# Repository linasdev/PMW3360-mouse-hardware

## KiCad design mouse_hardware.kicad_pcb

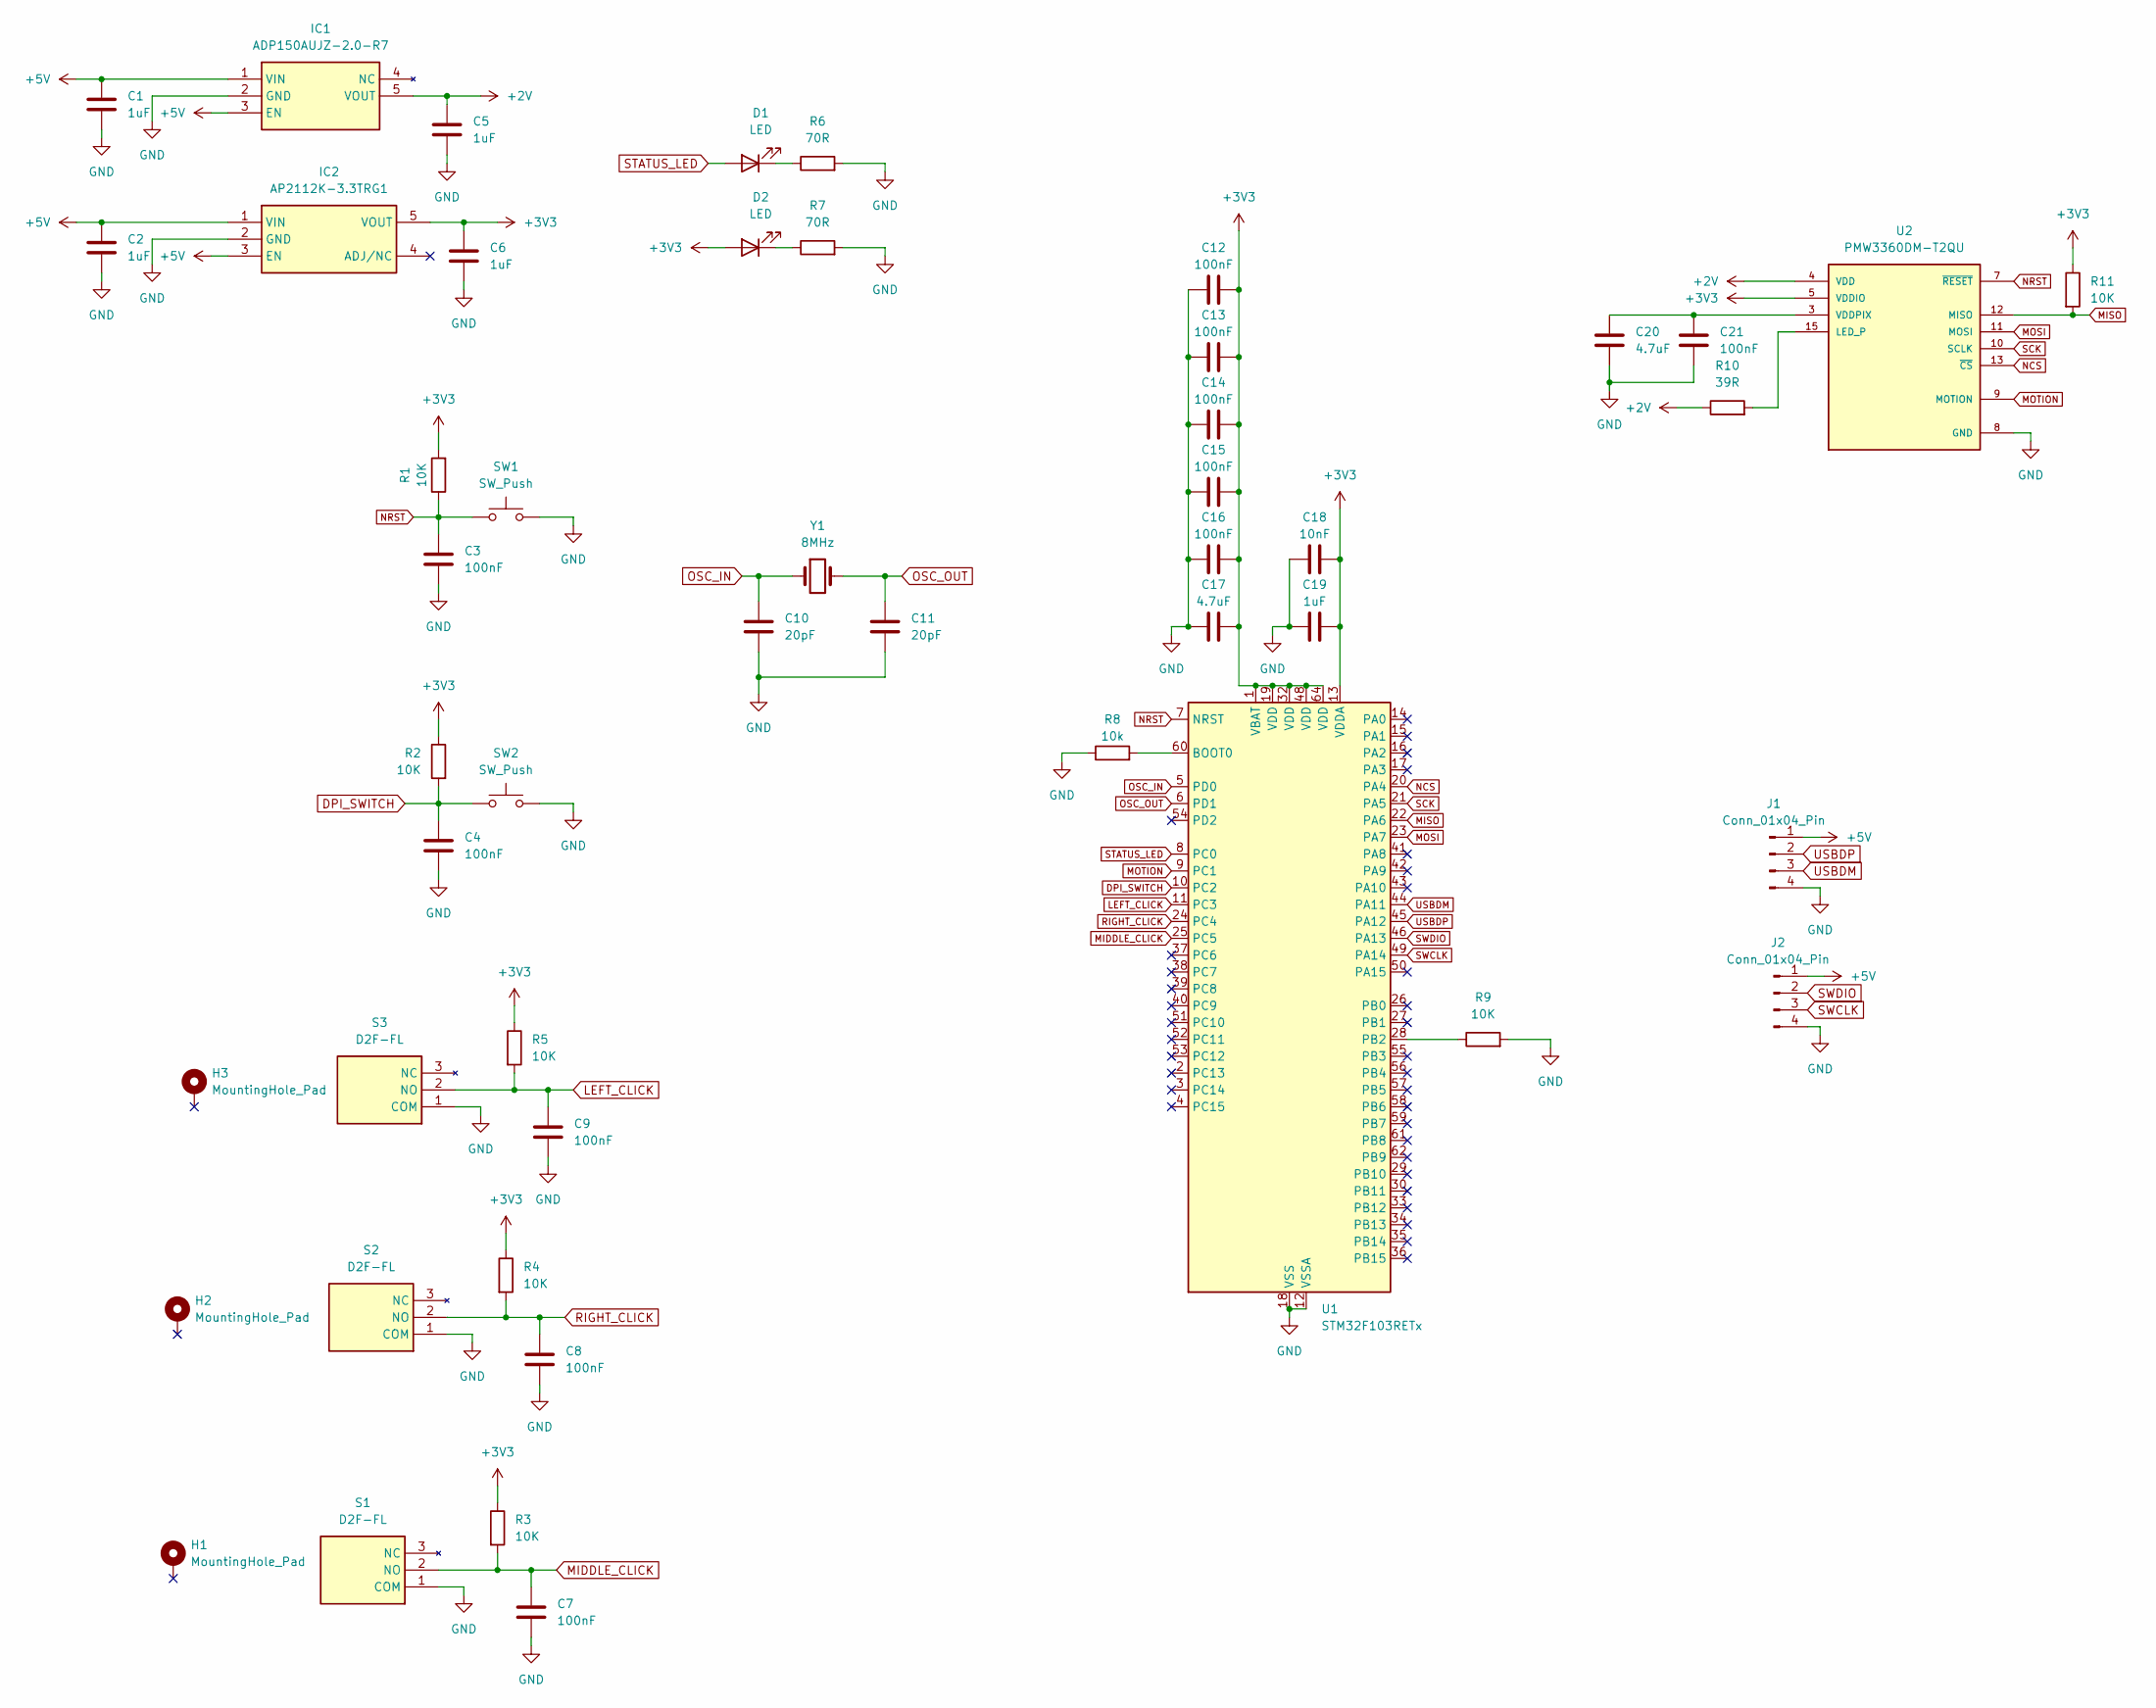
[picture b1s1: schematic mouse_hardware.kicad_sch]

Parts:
C1, C2, C5, C6, C19: 1uF; C_0805_2012Metric_Pad1.18x1.45mm_HandSolder
C3, C4, C7, C8, C9, C12, C13, C14, C15, C16, C21: 100nF; C_0805_2012Metric_Pad1.18x1.45mm_HandSolder
C10, C11: 20pF; C_0805_2012Metric_Pad1.18x1.45mm_HandSolder
C17, C20: 4.7uF; C_0805_2012Metric_Pad1.18x1.45mm_HandSolder
C18: 10nF; C_0805_2012Metric_Pad1.18x1.45mm_HandSolder
D1, D2: LED; LED_0805_2012Metric_Pad1.15x1.40mm_HandSolder
H1, H2, H3: MountingHole_Pad; Hole_1.8mm_1.2mm
IC1: ADP150AUJZ-2.0-R7; SOT95P280X100-5N; Mouser Part Number 584-ADP150AUJZ2.0R7
IC2: AP2112K-3.3TRG1; SOT95P282X130-5N; Mouser Part Number 621-AP2112K-3.3TRG1
J1, J2: Conn_01x04_Pin; PinHeader_1x04_P2.54mm_Horizontal
R1, R2, R3, R4, R5, R9, R11: 10K; R_0805_2012Metric_Pad1.20x1.40mm_HandSolder
R6, R7: 70R; R_0805_2012Metric_Pad1.20x1.40mm_HandSolder
R8: 10k; R_0805_2012Metric_Pad1.20x1.40mm_HandSolder
R10: 39R; R_0805_2012Metric_Pad1.20x1.40mm_HandSolder
S1, S2, S3: D2F-FL; D2FFL; Mouser Part Number 653-D2F-FL
SW1, SW2: SW_Push; 1478731
U1: STM32F103RETx; LQFP-64_10x10mm_P0.5mm
U2: PMW3360DM-T2QU; PMW3360; MANUFACTURER_PART_NUMBER PMW3360DM-T2QU
Y1: 8MHz; Crystal_SMD_HC49-SD_HandSoldering

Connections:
+2V: C5.2, IC1.5 (VOUT), R10.1, U2.4 (VDD)
+3V3: C6.2, C12.1, C13.1, C14.1, C15.1, C16.1, C17.1, C18.1, C19.1, D2.2 (A), IC2.5 (VOUT), R1.2, R2.1, R3.1, R4.1, R5.1, R11.1, U1.1 (VBAT), U1.13 (VDDA), U1.19 (VDD), U1.32 (VDD), U1.48 (VDD), U1.64 (VDD), U2.5 (VDDIO)
+5V: C1.2, C2.2, IC1.1 (VIN), IC1.3 (EN), IC2.1 (VIN), IC2.3 (EN), J1.1, J2.1
DPI_SWITCH: C4.1, R2.2, SW2.1, U1.10 (PC2)
GND: C1.1, C2.1, C3.2, C4.2, C5.1, C6.1, C7.2, C8.2, C9.2, C10.2, C11.2, C12.2, C13.2, C14.2, C15.2, C16.2, C17.2, C18.2, C19.2, C20.2, C21.2, IC1.2 (GND), IC2.2 (GND), J1.4, J2.4, R6.2, R7.2, R8.1, R9.2, S1.1 (COM), S2.1 (COM), S3.1 (COM), SW1.2, SW2.2, U1.12 (VSSA), U1.18 (VSS), U1.31 (VSS), U1.47 (VSS), U1.63 (VSS), U2.8 (GND)
LEFT_CLICK: C9.1, R5.2, S3.2 (NO), U1.11 (PC3)
MIDDLE_CLICK: C7.1, R3.2, S1.2 (NO), U1.25 (PC5)
MISO: R11.2, U1.22 (PA6), U2.12 (MISO)
MOSI: U1.23 (PA7), U2.11 (MOSI)
MOTION: U1.9 (PC1), U2.9 (MOTION)
NCS: U1.20 (PA4), U2.13 (~CS)
NRST: C3.1, R1.1, SW1.1, U1.7 (NRST), U2.7 (~RESET)
unnamed: D1.1 (K), R6.1
unnamed: D2.1 (K), R7.1
unnamed: R8.2, U1.60 (BOOT0)
unnamed: R9.1, U1.28 (PB2)
unnamed: R10.2, U2.15 (LED_P)
unnamed: C20.1, C21.1, U2.3 (VDDPIX)
OSC_IN: C10.1, U1.5 (PD0), Y1.1
OSC_OUT: C11.1, U1.6 (PD1), Y1.2
RIGHT_CLICK: C8.1, R4.2, S2.2 (NO), U1.24 (PC4)
SCK: U1.21 (PA5), U2.10 (SCLK)
STATUS_LED: D1.2 (A), U1.8 (PC0)
SWCLK: J2.3, U1.49 (PA14)
SWDIO: J2.2, U1.46 (PA13)
USBDM: J1.3, U1.44 (PA11)
USBDP: J1.2, U1.45 (PA12)

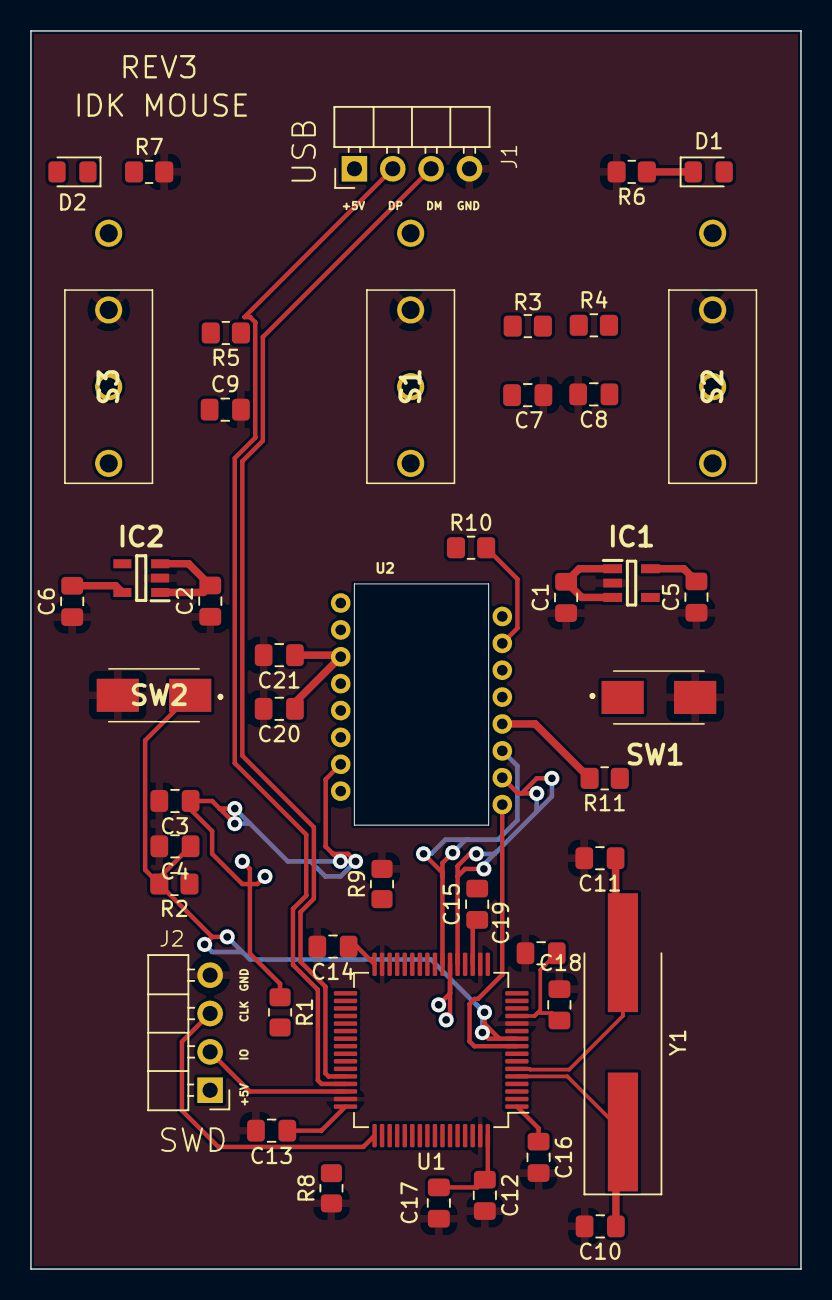
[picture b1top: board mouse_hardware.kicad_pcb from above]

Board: 4 copper layers, 51.0 x 82.0 mm, 49 parts (0 on the bottom side), 27 nets.

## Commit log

2024-02-04 Add .gitignore
2024-02-05 Edit .gitignore and add .README
2024-02-05 Edit README
2024-02-05 Start pcb schematic
2024-02-10 Start designing pcb
2024-02-26 Finish making schematic
2024-03-01 Start routing
2024-03-02 Finish designing and routing pcb
2024-04-04 Connect SCLK and SWDIO
2024-04-04 Move trace away from sensor
2024-04-12 Modify .gitignore
2024-04-12 Remove cached files
2024-04-12 Add connector labels
2024-04-23 rev3
2024-04-24 Convert files to newer KiCad format
2024-04-24 Move every part under part_library
2024-04-24 Improve schematic
2024-04-24 Re-reference and update pcb from schematic
2024-04-24 Start re-routing
